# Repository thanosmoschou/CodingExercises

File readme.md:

This repository contains various programming exercises in a plethora of programming languages.

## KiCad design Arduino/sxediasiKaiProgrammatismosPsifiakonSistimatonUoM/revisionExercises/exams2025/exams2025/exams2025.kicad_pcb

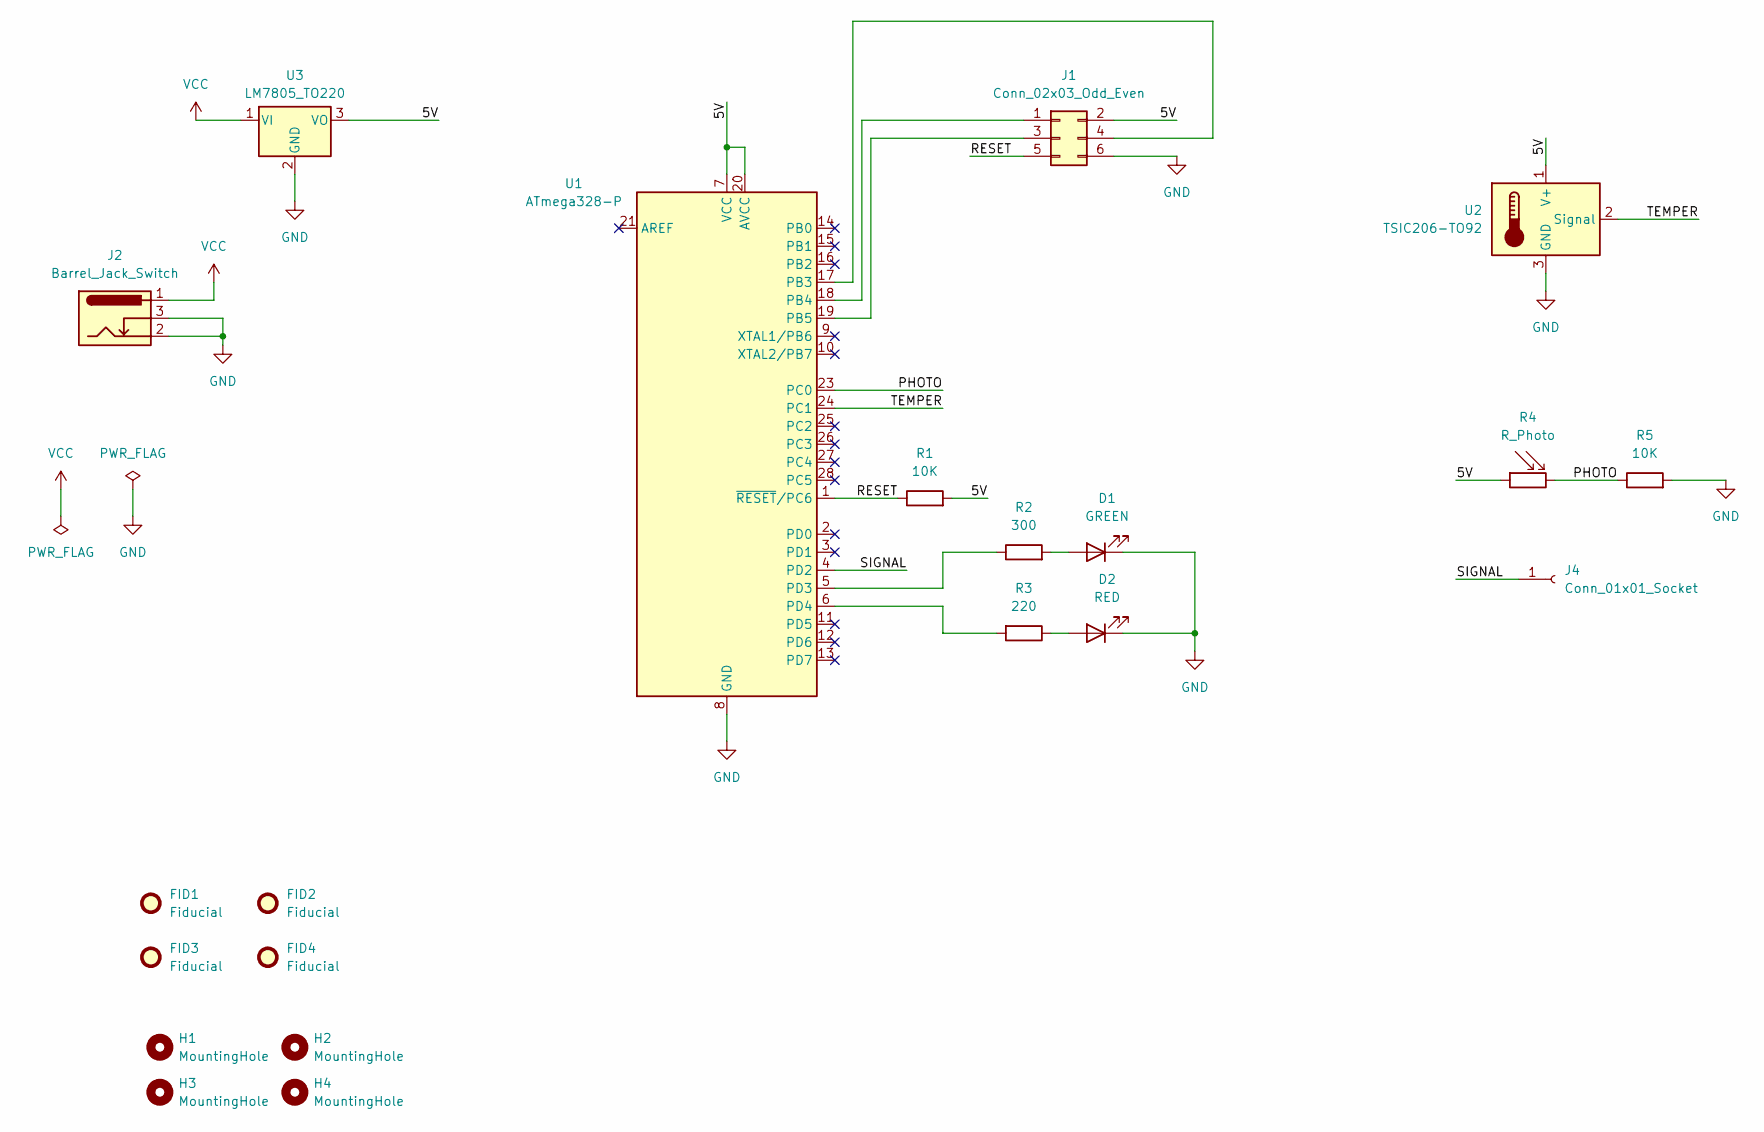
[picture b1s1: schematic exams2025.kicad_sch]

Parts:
D1: GREEN; LED_D5.0mm_Clear
D2: RED; LED_D5.0mm_Clear
FID1, FID2, FID3, FID4: Fiducial; Fiducial_1mm_Mask2mm
H1, H2, H3, H4: MountingHole; MountingHole_3.2mm_M3
J1: Conn_02x03_Odd_Even; PinHeader_2x03_P2.54mm_Vertical
J2: Barrel_Jack_Switch; BarrelJack_Horizontal
J4: Conn_01x01_Socket; Pin_D1.0mm_L10.0mm
R1, R5: 10K; R_Axial_DIN0207_L6.3mm_D2.5mm_P10.16mm_Horizontal
R2: 300; R_Axial_DIN0207_L6.3mm_D2.5mm_P10.16mm_Horizontal
R3: 220; R_Axial_DIN0207_L6.3mm_D2.5mm_P10.16mm_Horizontal
R4: R_Photo; R_LDR_5.1x4.3mm_P3.4mm_Vertical
U1: ATmega328-P; DIP-28_W7.62mm
U2: TSIC206-TO92; TO-92_Inline
U3: LM7805_TO220; TO-220-3_Vertical

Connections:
/5V: J1.2, R1.2, R4.1, U1.7 (VCC), U1.20 (AVCC), U2.1 (V+), U3.3 (VO)
/PHOTO: R4.2, R5.1, U1.23 (PC0)
/RESET: J1.5, R1.1, U1.1 (~RESET/PC6)
/SIGNAL: J4.1, U1.4 (PD2)
/TEMPER: U1.24 (PC1), U2.2 (Signal)
GND: D1.1 (K), D2.1 (K), J1.6, J2.2, J2.3, R5.2, U1.8 (GND), U1.22 (GND), U2.3 (GND), U3.2 (GND)
unnamed: D1.2 (A), R2.2
unnamed: D2.2 (A), R3.1
unnamed: J1.1, U1.18 (PB4)
unnamed: J1.3, U1.19 (PB5)
unnamed: J1.4, U1.17 (PB3)
unnamed: R2.1, U1.5 (PD3)
unnamed: R3.2, U1.6 (PD4)
VCC: J2.1, U3.1 (VI)

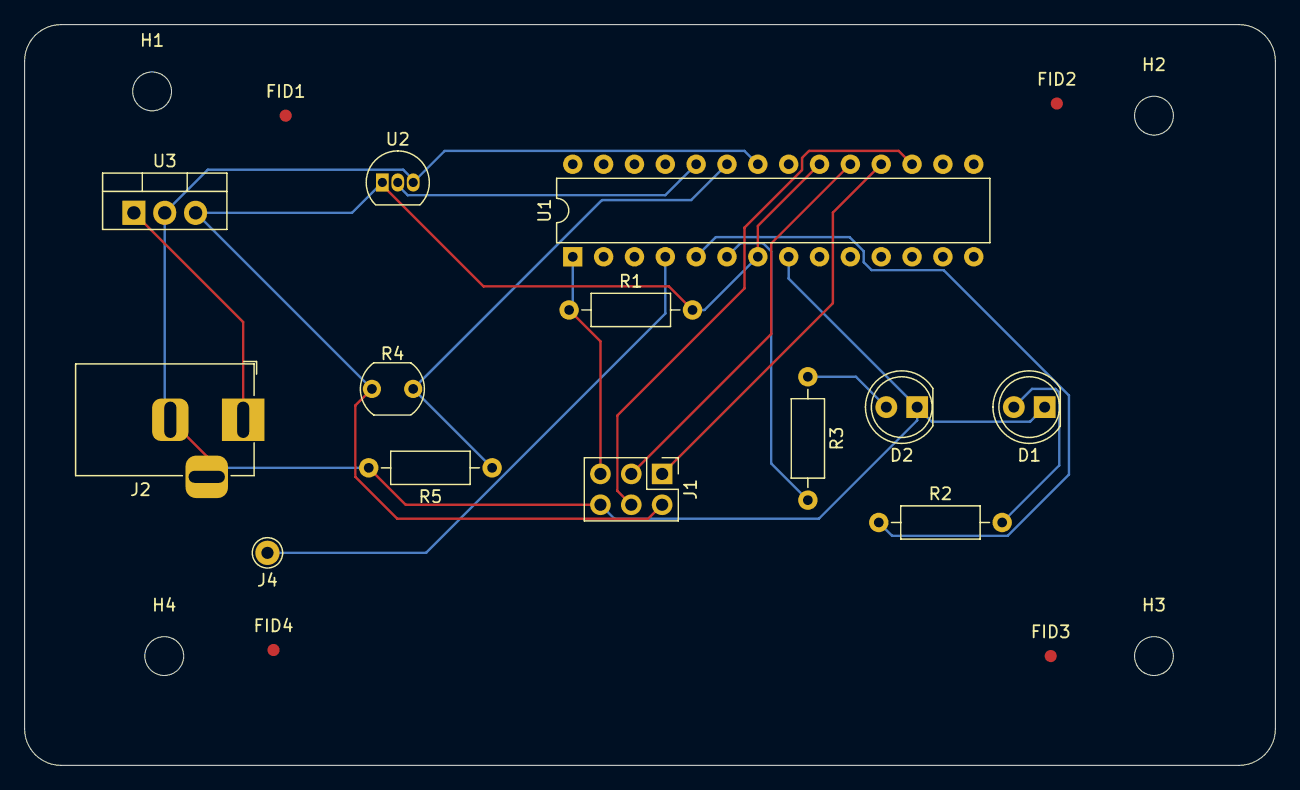
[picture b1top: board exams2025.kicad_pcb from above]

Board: 2 copper layers, 103.0 x 61.0 mm, 21 parts (0 on the bottom side), 14 nets.

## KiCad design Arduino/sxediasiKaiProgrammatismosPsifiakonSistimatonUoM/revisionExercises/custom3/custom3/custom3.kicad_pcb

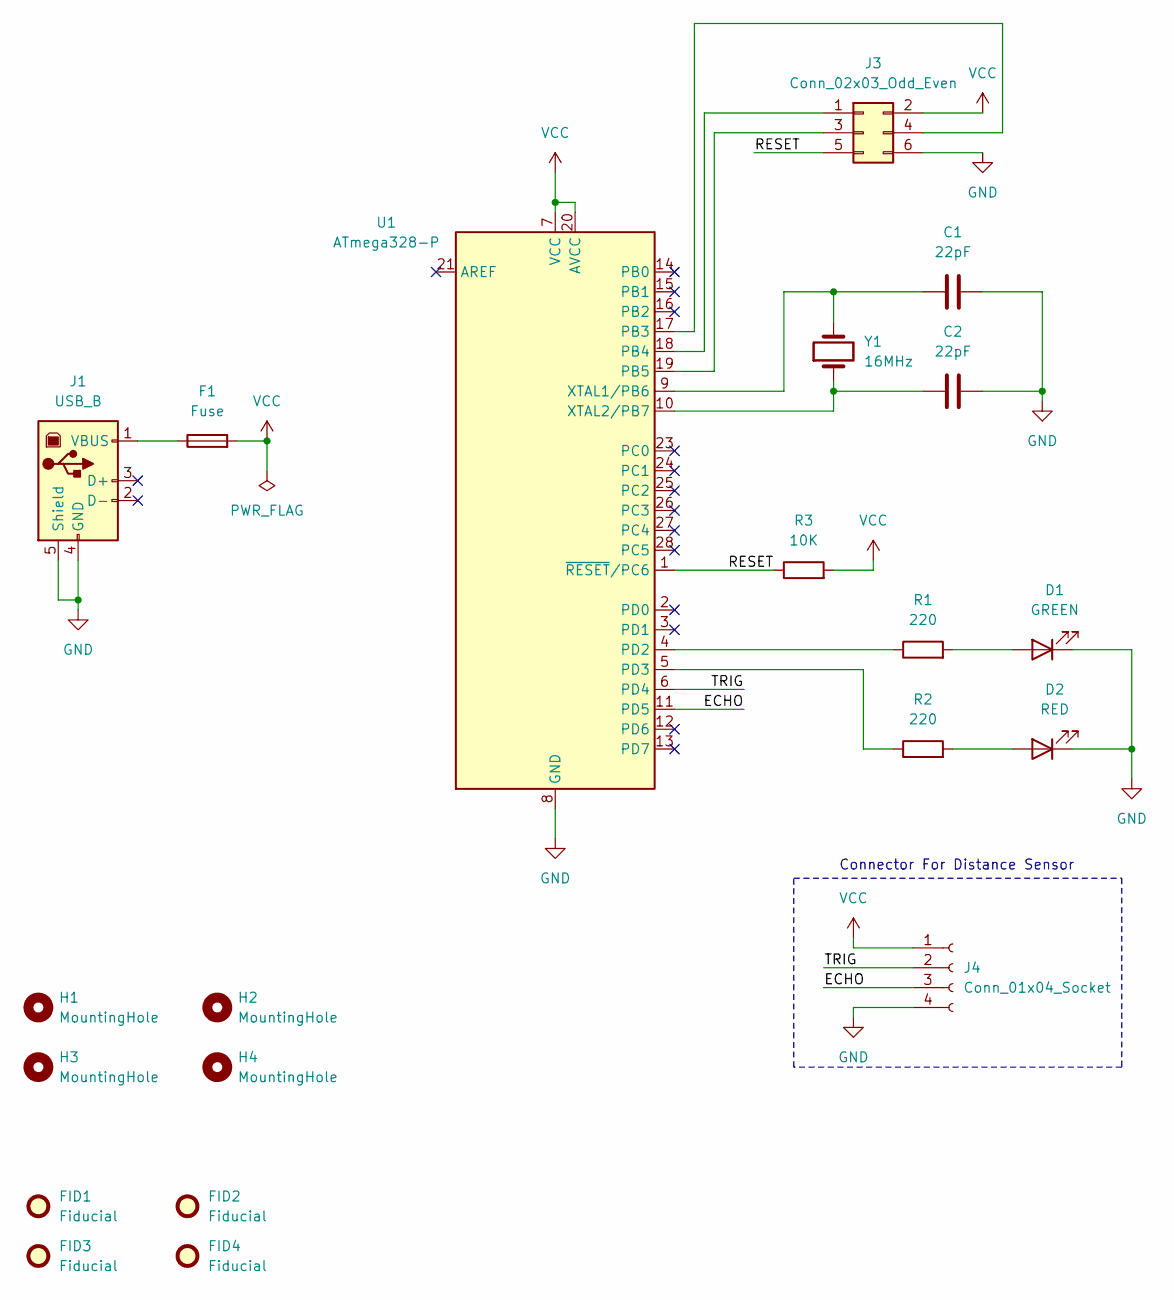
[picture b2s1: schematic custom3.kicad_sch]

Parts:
C1, C2: 22pF; C_0805_2012Metric
D1: GREEN; LED_0402_1005Metric
D2: RED; LED_0402_1005Metric
F1: Fuse; Fuse_1812_4532Metric
FID1, FID2, FID3, FID4: Fiducial; Fiducial_1mm_Mask2mm
H1, H2, H3, H4: MountingHole; MountingHole_3.2mm_M3
J1: USB_B; USB_B_OST_USB-B1HSxx_Horizontal
J3: Conn_02x03_Odd_Even; PinHeader_2x03_P2.54mm_Vertical
J4: Conn_01x04_Socket; Wuerth_WR-WTB_64800411622_1x04_P1.50mm_Vertical
R1, R2: 220; R_0805_2012Metric
R3: 10K; R_0805_2012Metric
U1: ATmega328-P; DIP-28_W7.62mm
Y1: 16MHz; Crystal_HC49-4H_Vertical

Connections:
/ECHO: J4.3, U1.11 (PD5)
/RESET: J3.5, R3.1, U1.1 (~RESET/PC6)
/TRIG: J4.2, U1.6 (PD4)
GND: C1.2, C2.2, D1.1 (K), D2.1 (K), J1.4 (GND), J1.5 (Shield), J3.6, J4.4, U1.8 (GND), U1.22 (GND)
unnamed: D1.2 (A), R1.2
unnamed: D2.2 (A), R2.2
unnamed: F1.1, J1.1 (VBUS)
unnamed: J3.1, U1.18 (PB4)
unnamed: J3.3, U1.19 (PB5)
unnamed: J3.4, U1.17 (PB3)
unnamed: R1.1, U1.4 (PD2)
unnamed: R2.1, U1.5 (PD3)
unnamed: C1.1, U1.9 (XTAL1/PB6), Y1.2
unnamed: C2.1, U1.10 (XTAL2/PB7), Y1.1
VCC: F1.2, J3.2, J4.1, R3.2, U1.7 (VCC), U1.20 (AVCC)

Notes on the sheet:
Connector For Distance Sensor

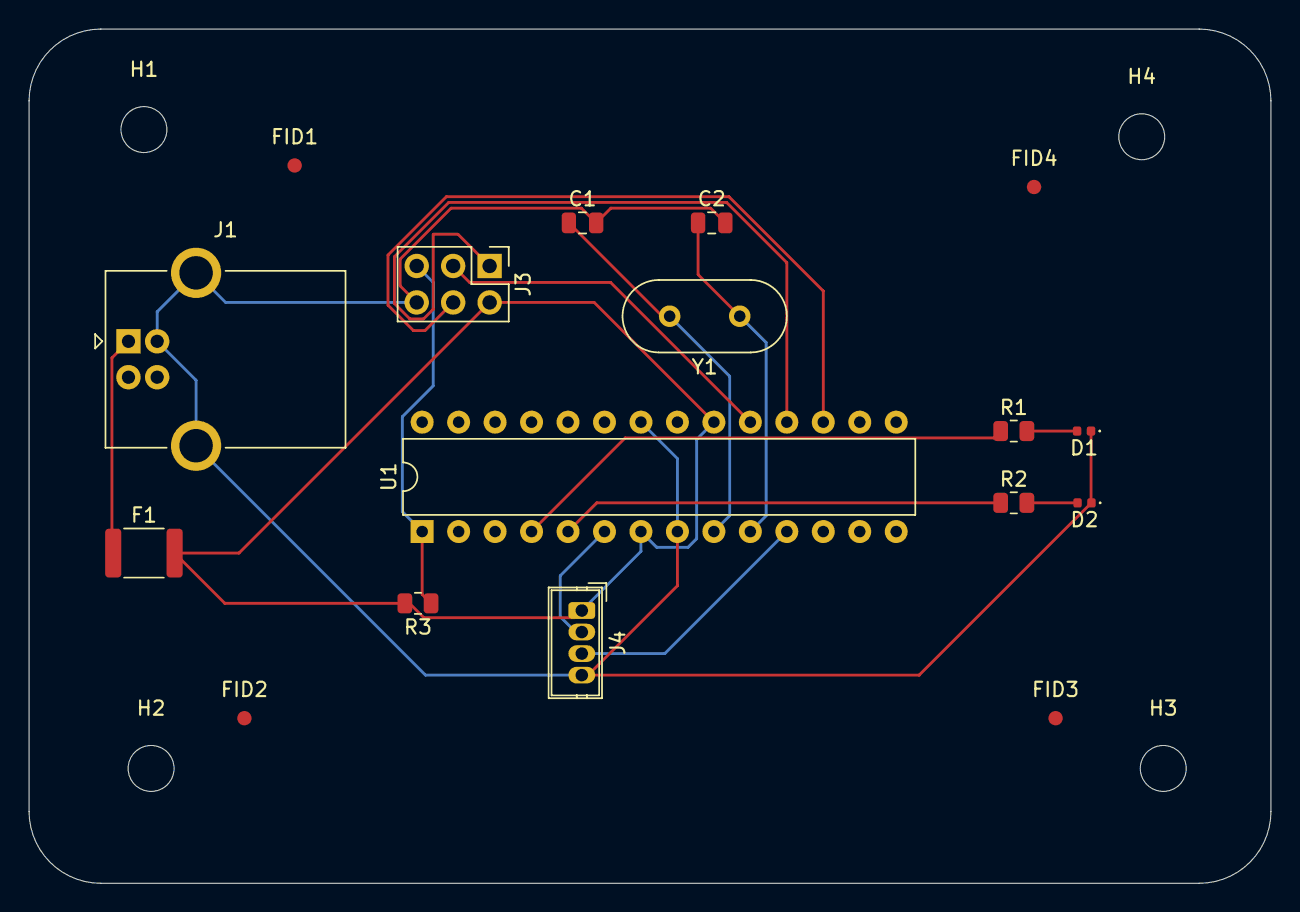
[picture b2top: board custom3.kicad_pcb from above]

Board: 2 copper layers, 86.5 x 59.5 mm, 21 parts (0 on the bottom side), 15 nets.

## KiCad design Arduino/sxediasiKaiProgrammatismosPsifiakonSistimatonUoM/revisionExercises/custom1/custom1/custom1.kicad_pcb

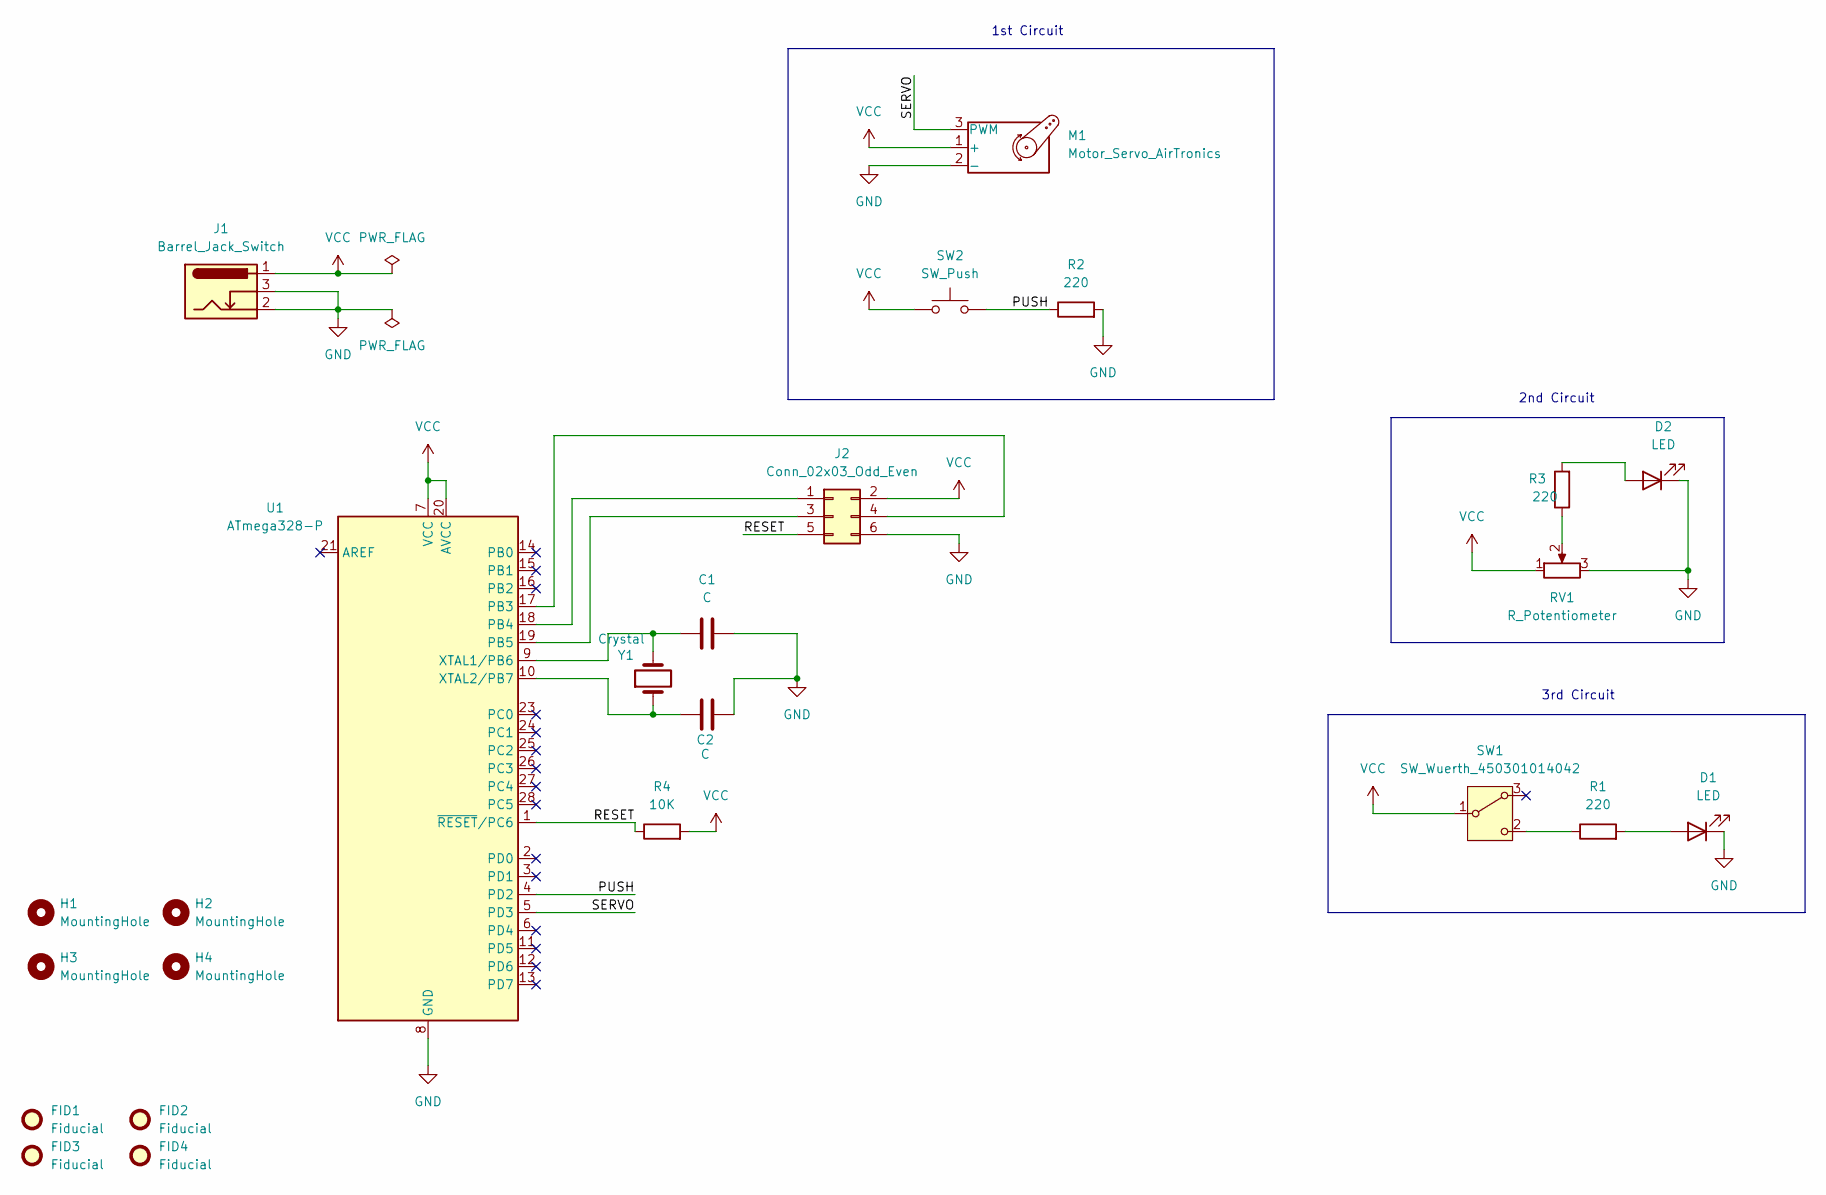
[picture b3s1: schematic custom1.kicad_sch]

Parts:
C1, C2: C; C_0805_2012Metric
D1, D2: LED; LED_0402_1005Metric
FID1, FID2, FID3, FID4: Fiducial; Fiducial_1mm_Mask2mm
H1, H2, H3, H4: MountingHole; MountingHole_3.2mm_M3
J1: Barrel_Jack_Switch; BarrelJack_Horizontal
J2: Conn_02x03_Odd_Even; PinHeader_2x03_P2.54mm_Vertical
M1: Motor_Servo_AirTronics; PinHeader_1x03_P2.54mm_Horizontal
R1, R2, R3: 220; R_Axial_DIN0207_L6.3mm_D2.5mm_P10.16mm_Horizontal
R4: 10K; R_Axial_DIN0207_L6.3mm_D2.5mm_P10.16mm_Horizontal
RV1: R_Potentiometer; Potentiometer_Bourns_3314G_Vertical
SW1: SW_Wuerth_450301014042; SW_Slide-03_Wuerth-WS-SLTV_10x2.5x6.4_P2.54mm
SW2: SW_Push; SW_Push_1P1T_XKB_TS-1187A
U1: ATmega328-P; DIP-28_W7.62mm
Y1: Crystal; Crystal_HC49-4H_Vertical

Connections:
/PUSH: R2.1, SW2.2, U1.4 (PD2)
/RESET: J2.5, R4.1, U1.1 (~RESET/PC6)
/SERVO: M1.3 (PWM), U1.5 (PD3)
GND: C1.2, C2.2, D1.1 (K), D2.1 (K), J1.2, J1.3, J2.6, M1.2 (-), R2.2, RV1.3, U1.8 (GND), U1.22 (GND)
unnamed: D1.2 (A), R1.2
unnamed: D2.2 (A), R3.2
unnamed: J2.1, U1.18 (PB4)
unnamed: J2.3, U1.19 (PB5)
unnamed: J2.4, U1.17 (PB3)
unnamed: R3.1, RV1.2
unnamed: R1.1, SW1.2 (C)
unnamed: C1.1, U1.9 (XTAL1/PB6), Y1.2
unnamed: C2.1, U1.10 (XTAL2/PB7), Y1.1
VCC: J1.1, J2.2, M1.1 (+), R4.2, RV1.1, SW1.1 (B), SW2.1, U1.7 (VCC), U1.20 (AVCC)

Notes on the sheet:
2nd Circuit
1st Circuit
3rd Circuit

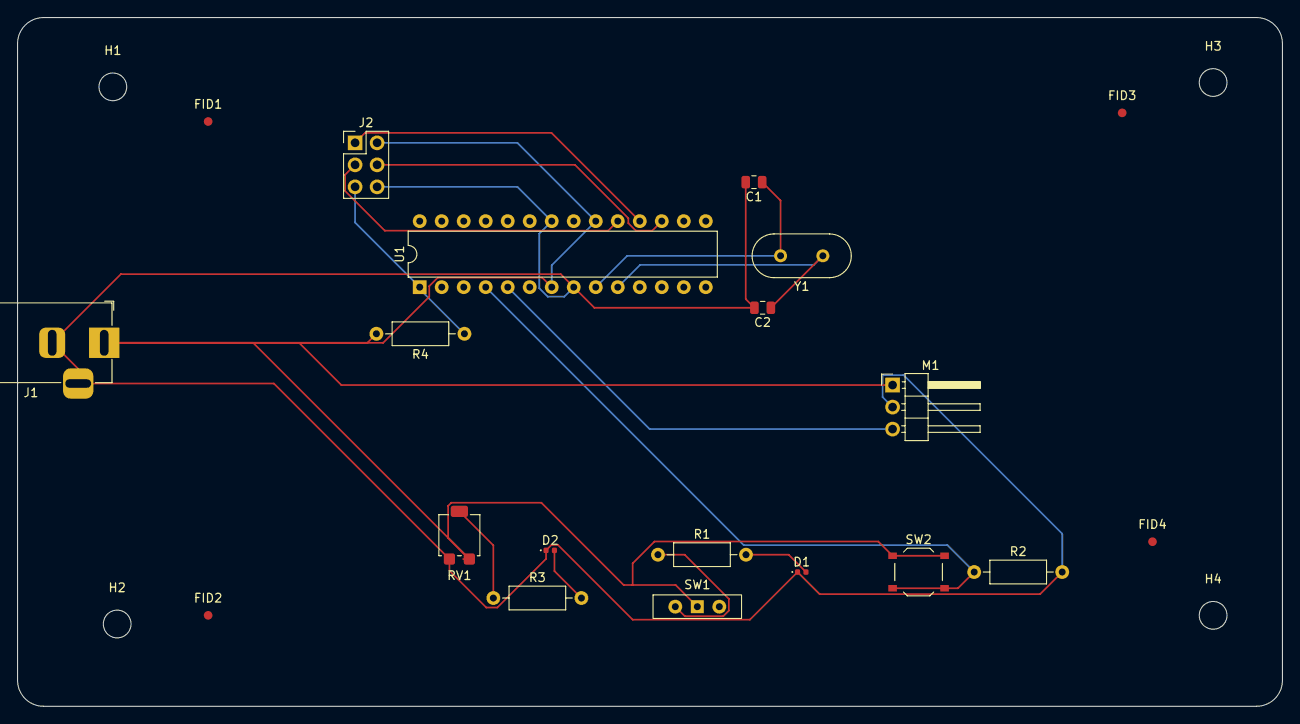
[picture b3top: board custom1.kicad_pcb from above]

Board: 2 copper layers, 146.0 x 79.5 mm, 24 parts (0 on the bottom side), 14 nets.

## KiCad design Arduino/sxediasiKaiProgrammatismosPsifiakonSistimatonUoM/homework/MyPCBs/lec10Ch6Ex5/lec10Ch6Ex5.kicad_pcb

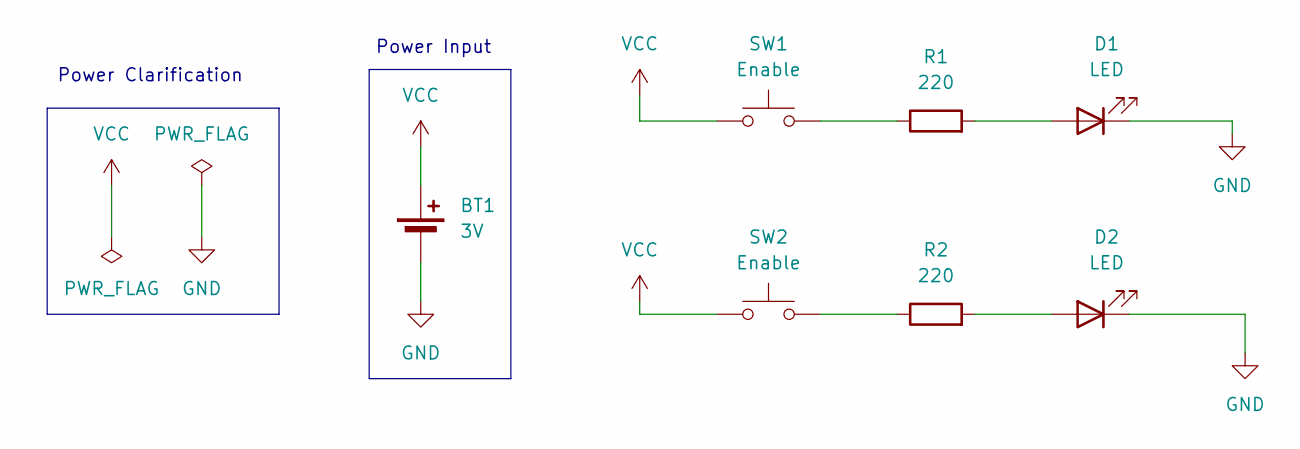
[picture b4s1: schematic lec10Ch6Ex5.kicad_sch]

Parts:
BT1: 3V; BatteryHolder_Keystone_103_1x20mm
D1, D2: LED; LED_D5.0mm_Clear
R1, R2: 220; R_Axial_DIN0207_L6.3mm_D2.5mm_P10.16mm_Horizontal
SW1, SW2: Enable; SW_PUSH_6mm_H5mm

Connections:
GND: BT1.2 (-), D1.1 (K), D2.1 (K)
unnamed: D1.2 (A), R1.2
unnamed: D2.2 (A), R2.2
unnamed: R1.1, SW1.2
unnamed: R2.1, SW2.2
VCC: BT1.1 (+), SW1.1, SW2.1

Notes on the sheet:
Power Clarification
Power Input

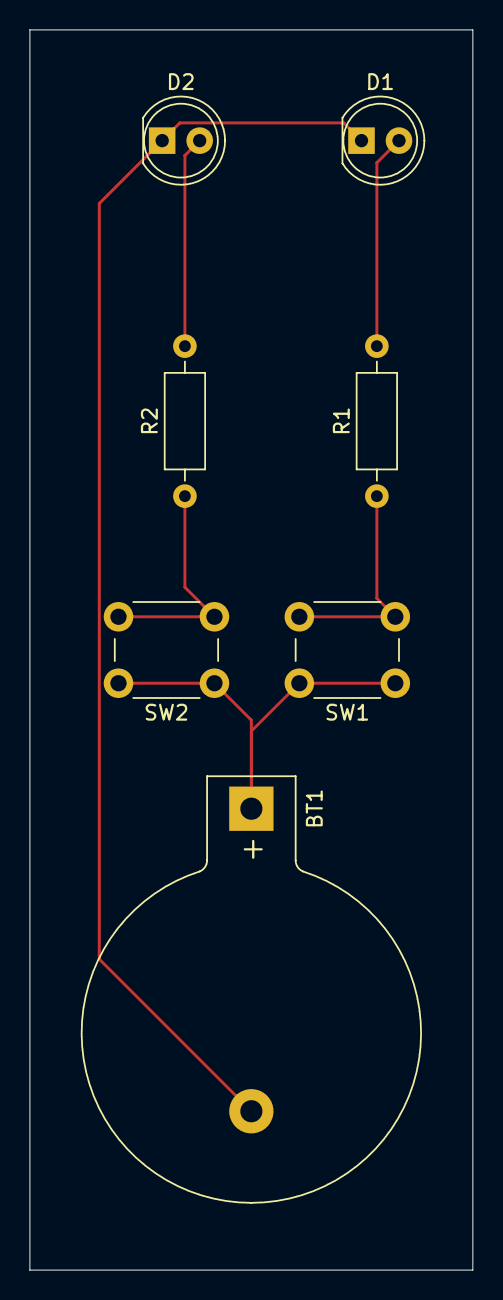
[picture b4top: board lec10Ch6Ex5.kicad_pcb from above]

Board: 2 copper layers, 30.0 x 84.0 mm, 7 parts (0 on the bottom side), 6 nets.

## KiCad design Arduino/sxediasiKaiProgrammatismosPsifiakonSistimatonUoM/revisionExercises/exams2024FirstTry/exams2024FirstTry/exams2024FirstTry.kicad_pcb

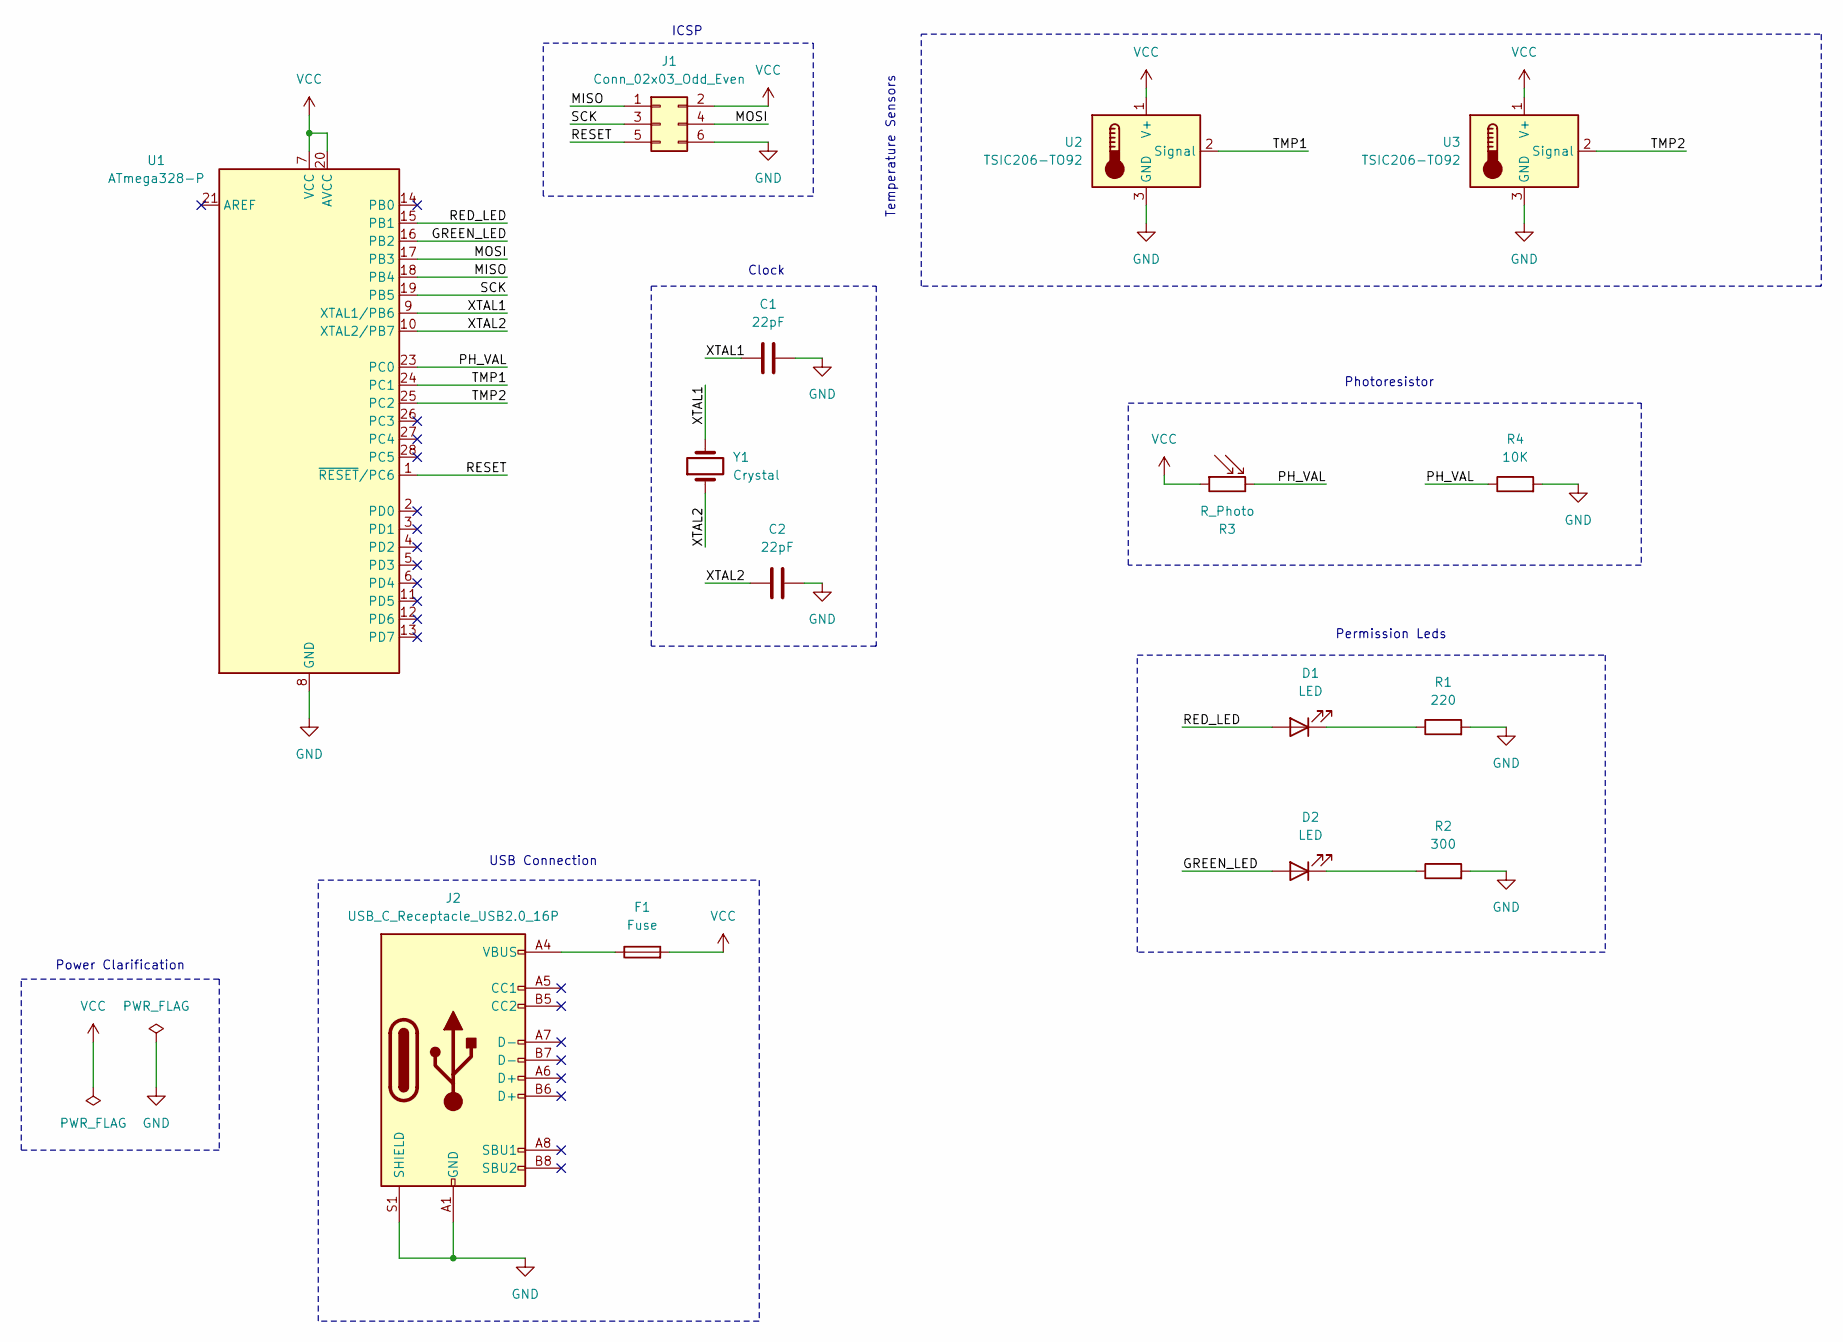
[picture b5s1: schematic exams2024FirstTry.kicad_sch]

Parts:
C1, C2: 22pF; C_Disc_D6.0mm_W4.4mm_P5.00mm
D1, D2: LED; LED_D5.0mm_Clear
F1: Fuse; Fuse_0402_1005Metric
J1: Conn_02x03_Odd_Even; PinHeader_2x03_P2.54mm_Vertical
J2: USB_C_Receptacle_USB2.0_16P; USB_C_Receptacle_Amphenol_124019772112A
R1: 220; R_Axial_DIN0207_L6.3mm_D2.5mm_P10.16mm_Horizontal
R2: 300; R_Axial_DIN0207_L6.3mm_D2.5mm_P10.16mm_Horizontal
R3: R_Photo; R_LDR_5.1x4.3mm_P3.4mm_Vertical
R4: 10K; R_Axial_DIN0207_L6.3mm_D2.5mm_P10.16mm_Horizontal
U1: ATmega328-P; DIP-28_W7.62mm
U2, U3: TSIC206-TO92; TO-92_Inline
Y1: Crystal; Crystal_HC49-4H_Vertical

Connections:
/GREEN_LED: D2.2 (A), U1.16 (PB2)
/MISO: J1.1, U1.18 (PB4)
/MOSI: J1.4, U1.17 (PB3)
/PH_VAL: R3.2, R4.1, U1.23 (PC0)
/RED_LED: D1.2 (A), U1.15 (PB1)
/RESET: J1.5, U1.1 (~RESET/PC6)
/SCK: J1.3, U1.19 (PB5)
/TMP1: U1.24 (PC1), U2.2 (Signal)
/TMP2: U1.25 (PC2), U3.2 (Signal)
/XTAL1: C1.1, U1.9 (XTAL1/PB6), Y1.2
/XTAL2: C2.1, U1.10 (XTAL2/PB7), Y1.1
GND: C1.2, C2.2, J1.6, J2.A1 (GND), J2.A12 (GND), J2.B1 (GND), J2.B12 (GND), J2.S1 (SHIELD), R1.2, R2.2, R4.2, U1.8 (GND), U1.22 (GND), U2.3 (GND), U3.3 (GND)
unnamed: D1.1 (K), R1.1
unnamed: D2.1 (K), R2.1
unnamed: F1.1, J2.A4 (VBUS), J2.A9 (VBUS), J2.B4 (VBUS), J2.B9 (VBUS)
VCC: F1.2, J1.2, R3.1, U1.7 (VCC), U1.20 (AVCC), U2.1 (V+), U3.1 (V+)

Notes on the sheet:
Temperature Sensors
Permission Leds
Photoresistor
USB Connection
Power Clarification
Clock
ICSP

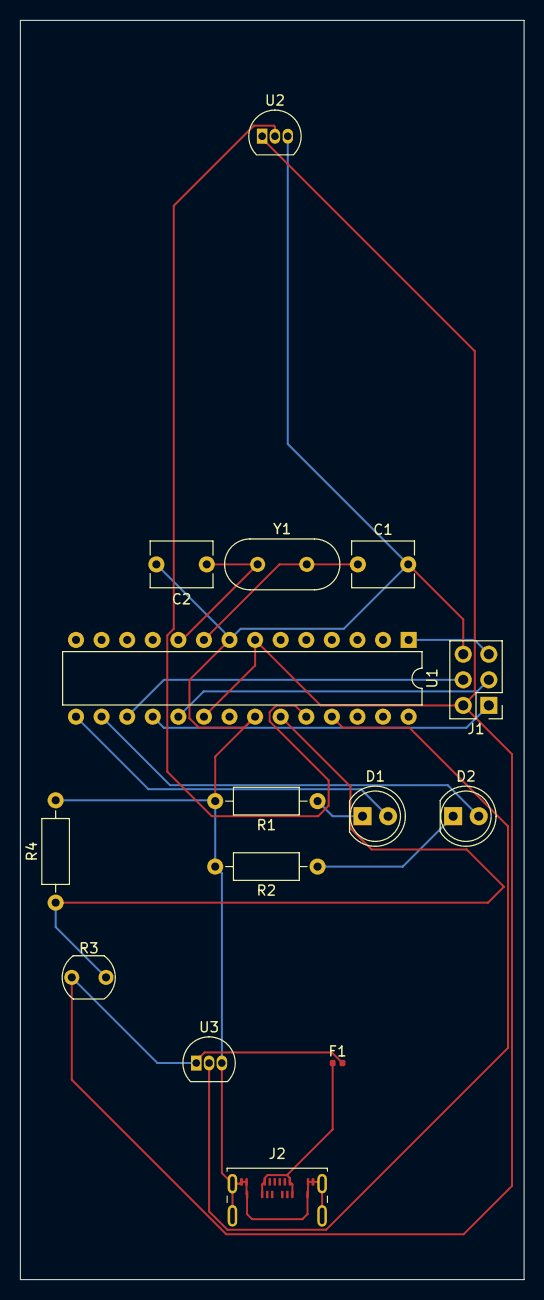
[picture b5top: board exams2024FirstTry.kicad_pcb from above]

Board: 2 copper layers, 50.0 x 125.0 mm, 15 parts (0 on the bottom side), 16 nets.

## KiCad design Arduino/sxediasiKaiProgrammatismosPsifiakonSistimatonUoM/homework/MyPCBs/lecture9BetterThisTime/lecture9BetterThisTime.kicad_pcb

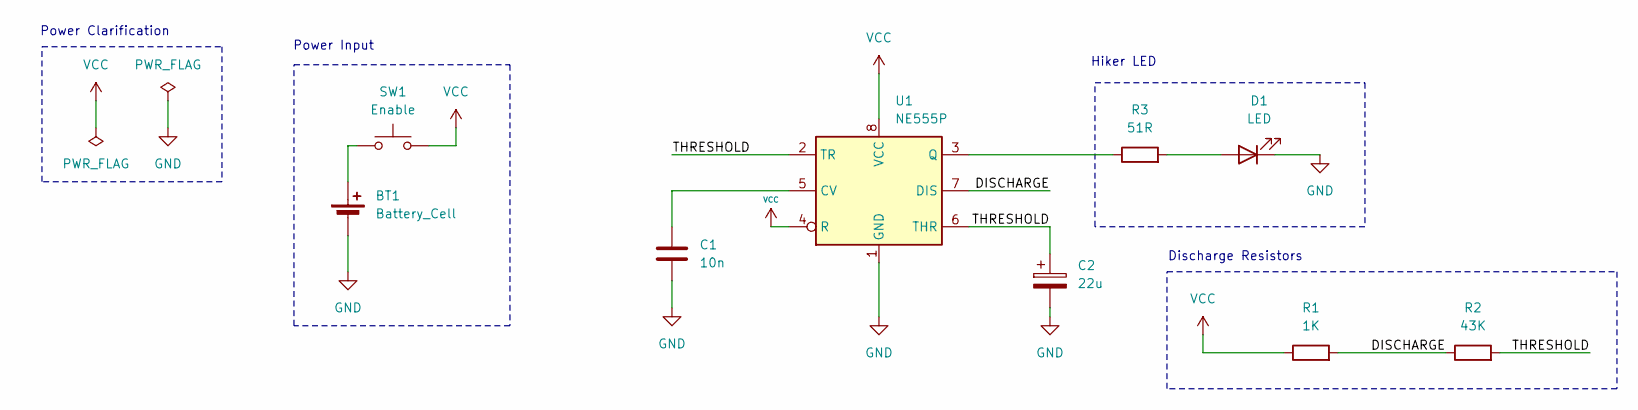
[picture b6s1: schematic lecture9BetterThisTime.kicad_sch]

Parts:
BT1: Battery_Cell; BatteryHolder_Keystone_103_1x20mm
C1: 10n; C_Disc_D6.0mm_W4.4mm_P5.00mm
C2: 22u; CP_Radial_D6.3mm_P2.50mm
D1: LED; LED_D5.0mm_Clear
R1: 1K; R_Axial_DIN0207_L6.3mm_D2.5mm_P10.16mm_Horizontal
R2: 43K; R_Axial_DIN0207_L6.3mm_D2.5mm_P10.16mm_Horizontal
R3: 51R; R_Axial_DIN0207_L6.3mm_D2.5mm_P10.16mm_Horizontal
SW1: Enable; SW_PUSH_6mm_H5mm
U1: NE555P; DIP-8_W7.62mm

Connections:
/DISCHARGE: R1.2, R2.1, U1.7 (DIS)
/THRESHOLD: C2.1, R2.2, U1.2 (TR), U1.6 (THR)
GND: BT1.2 (-), C1.2, C2.2, D1.1 (K), U1.1 (GND)
unnamed: BT1.1 (+), SW1.1
unnamed: D1.2 (A), R3.2
unnamed: C1.1, U1.5 (CV)
unnamed: R3.1, U1.3 (Q)
VCC: R1.1, SW1.2, U1.4 (R), U1.8 (VCC)

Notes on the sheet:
Power Input
Hiker LED
Discharge Resistors
Power Clarification

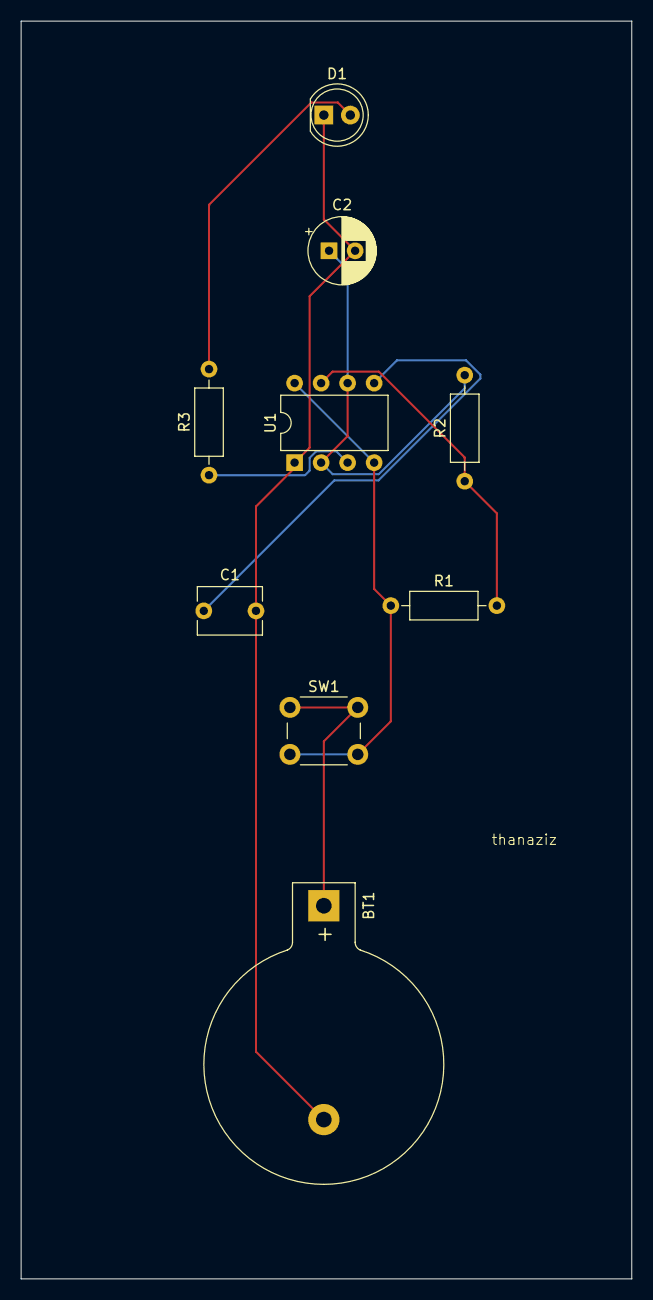
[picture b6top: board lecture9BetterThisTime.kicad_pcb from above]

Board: 2 copper layers, 58.5 x 120.5 mm, 9 parts (0 on the bottom side), 8 nets.

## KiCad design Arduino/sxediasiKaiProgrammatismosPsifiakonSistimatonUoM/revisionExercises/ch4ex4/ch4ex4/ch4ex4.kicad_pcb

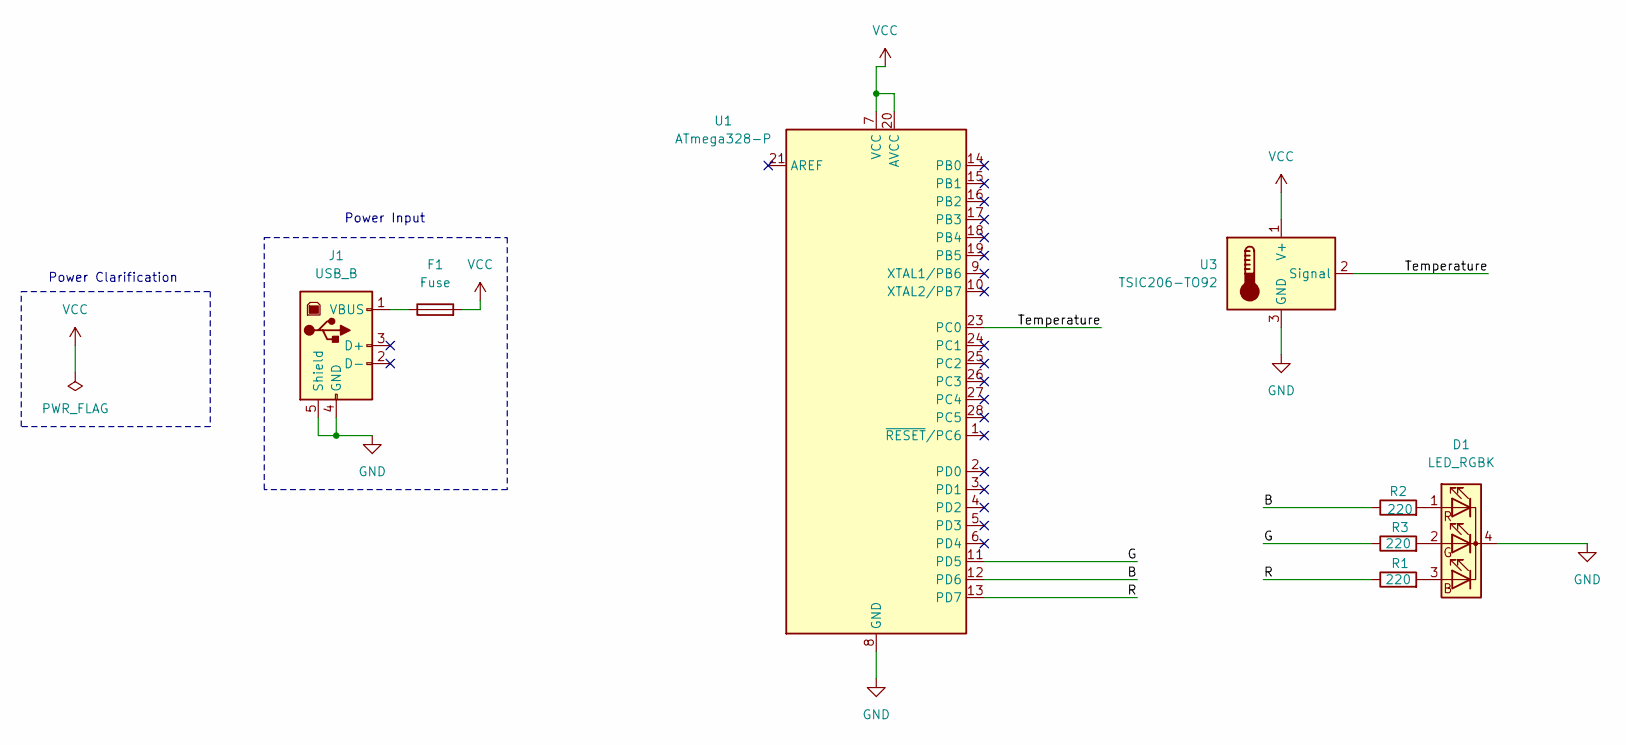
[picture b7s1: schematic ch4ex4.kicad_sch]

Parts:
D1: LED_RGBK; LED_RGB_1210
F1: Fuse; Fuse_0402_1005Metric
J1: USB_B; USB_B_Lumberg_2411_02_Horizontal
R1, R2, R3: 220; R_Axial_DIN0207_L6.3mm_D2.5mm_P10.16mm_Horizontal
U1: ATmega328-P; DIP-28_W7.62mm
U3: TSIC206-TO92; TO-92_Inline

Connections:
/B: R2.1, U1.12 (PD6)
/G: R3.1, U1.11 (PD5)
/R: R1.1, U1.13 (PD7)
/Temperature: U1.23 (PC0), U3.2 (Signal)
GND: D1.4 (K), J1.4 (GND), J1.5 (Shield), U1.8 (GND), U1.22 (GND), U3.3 (GND)
unnamed: D1.3 (BA), R1.2
unnamed: D1.2 (GA), R3.2
unnamed: D1.1 (RA), R2.2
unnamed: F1.1, J1.1 (VBUS)
VCC: F1.2, U1.7 (VCC), U1.20 (AVCC), U3.1 (V+)

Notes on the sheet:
Power Clarification
Power Input

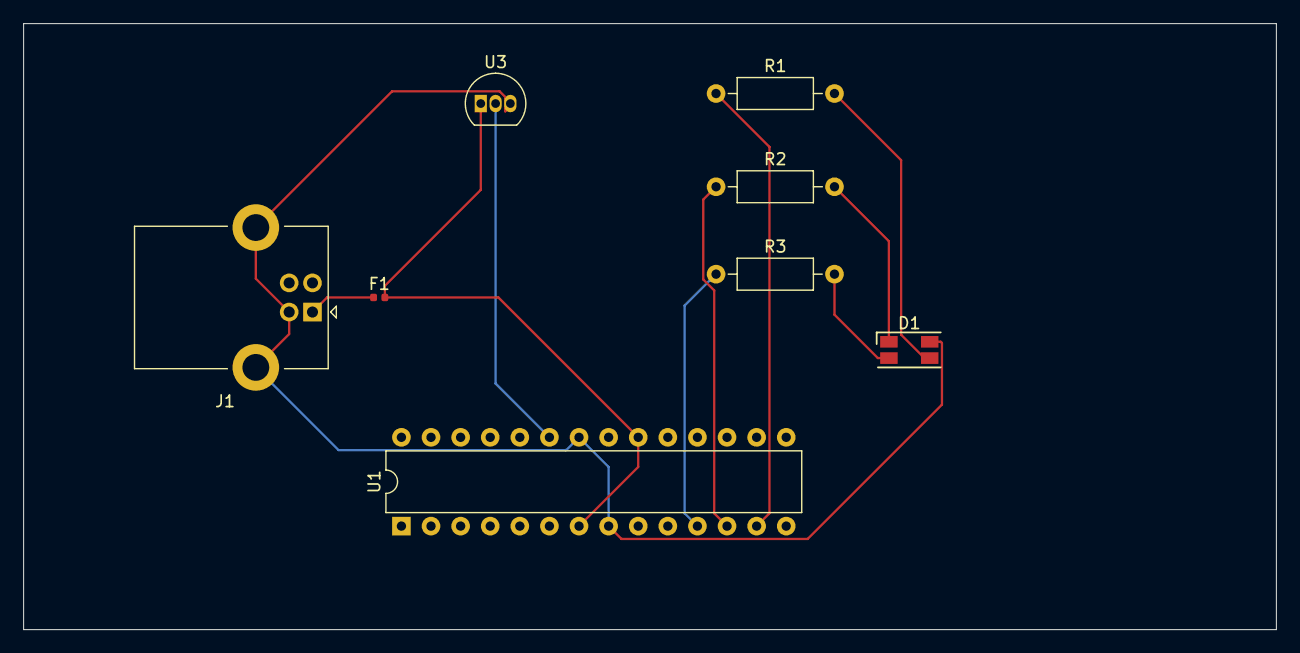
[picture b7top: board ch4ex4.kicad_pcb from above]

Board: 2 copper layers, 107.5 x 52.0 mm, 8 parts (0 on the bottom side), 10 nets.
